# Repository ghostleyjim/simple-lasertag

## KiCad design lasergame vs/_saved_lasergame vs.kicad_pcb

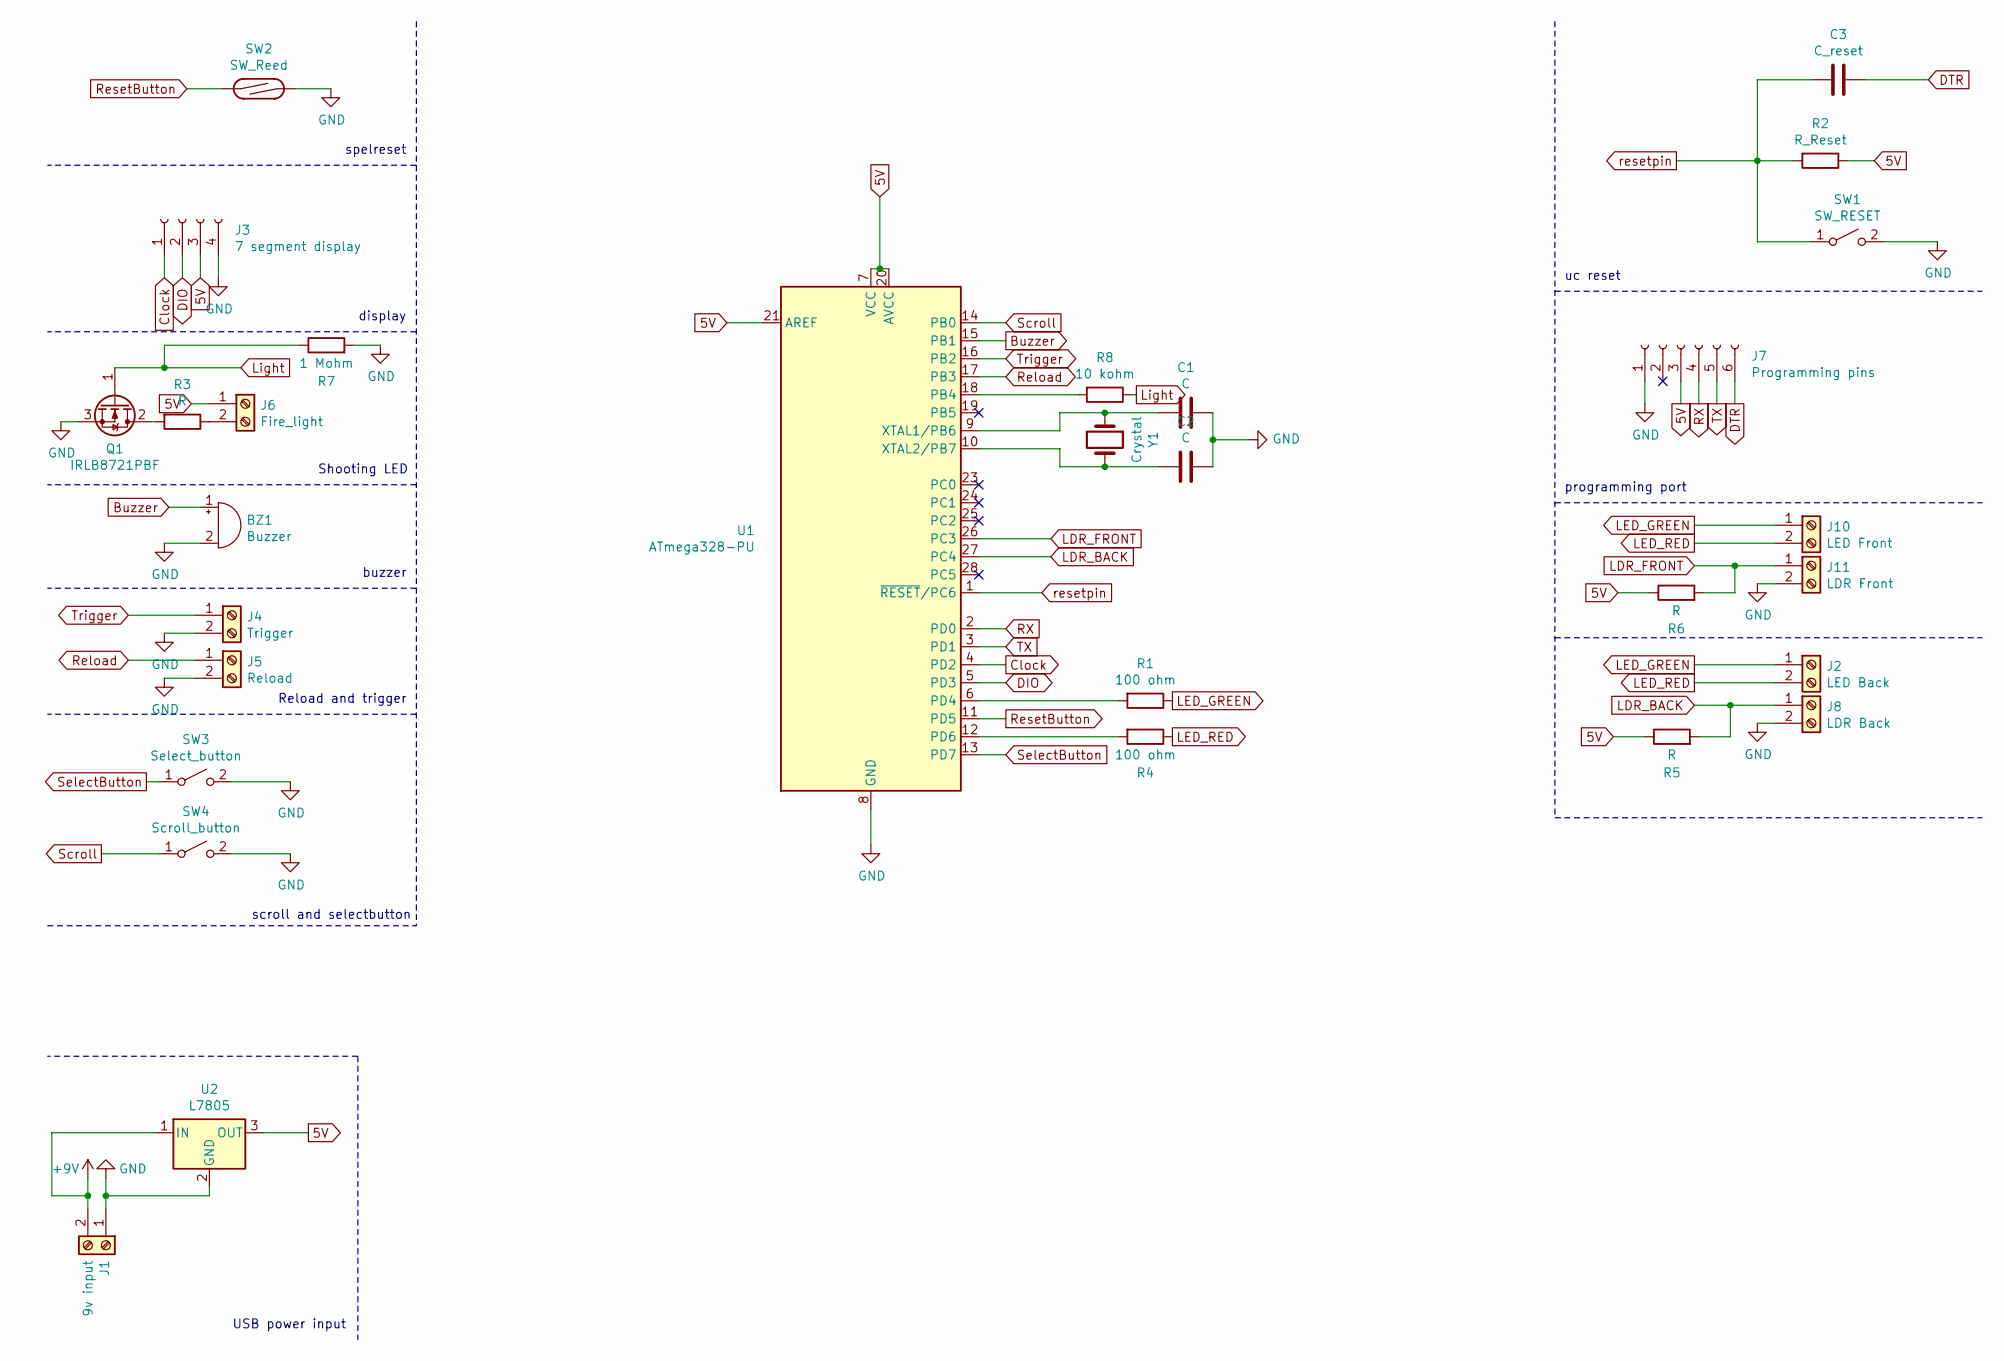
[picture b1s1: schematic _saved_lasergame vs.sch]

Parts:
BZ1: Buzzer; Buzzer_12x9.5RM7.6
C1, C2: C; C_Disc_D5.0mm_W2.5mm_P2.50mm
C3: C_reset; C_Disc_D5.0mm_W2.5mm_P2.50mm
J1: 9v input; TerminalBlock_Phoenix_MKDS-1,5-2-5.08_1x02_P5.08mm_Horizont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
J2: LED Back; TerminalBlock_Phoenix_MKDS-1,5-2-5.08_1x02_P5.08mm_Horizont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
J3: 7 segment display; PinHeader_1x04_P2.54mm_Vertical
J4: Trigger; TerminalBlock_Phoenix_MKDS-1,5-2-5.08_1x02_P5.08mm_Horizont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
J5: Reload; TerminalBlock_Phoenix_MKDS-1,5-2-5.08_1x02_P5.08mm_Horizont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
J6: Fire_light; TerminalBlock_Phoenix_MKDS-1,5-2-5.08_1x02_P5.08mm_Horizont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
J7: Programming pins; PinHeader_1x06_P2.54mm_Vertical
J8: LDR Back; TerminalBlock_Phoenix_MKDS-1,5-2-5.08_1x02_P5.08mm_Horizont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
J10: LED Front; TerminalBlock_Phoenix_MKDS-1,5-2-5.08_1x02_P5.08mm_Horizont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
J11: LDR Front; TerminalBlock_Phoenix_MKDS-1,5-2-5.08_1x02_P5.08mm_Horizont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
Q1: IRLB8721PBF; TO-220-3_Vertical
R1, R4: 100 ohm; R_Axial_DIN0309_L9.0mm_D3.2mm_P12.70mm_Horizontal
R2: R_Reset; R_Axial_DIN0309_L9.0mm_D3.2mm_P12.70mm_Horizontal
R3: R; R_Axial_DIN0516_L15.5mm_D5.0mm_P20.32mm_Horizontal
R5, R6: R; R_Axial_DIN0309_L9.0mm_D3.2mm_P12.70mm_Horizontal
R7: 1 Mohm; R_Axial_DIN0309_L9.0mm_D3.2mm_P12.70mm_Horizontal
R8: 10 kohm; R_Axial_DIN0309_L9.0mm_D3.2mm_P12.70mm_Horizontal
SW1: SW_RESET; SW_PUSH_6mm_H9.5mm
SW2: SW_Reed; Reed Switch THT
SW3: Select_button; SW_PUSH_6mm_H9.5mm
SW4: Scroll_button; SW_PUSH_6mm_H9.5mm
U1: ATmega328-PU; DIP-28_W7.62mm_Socket
U2: L7805; TO-220-3_Vertical
Y1: Crystal; Crystal_HC49-U_Vertical

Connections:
5V: J3.3, J6.1, J7.3, R2.1, R5.1, R6.1, U1.7 (VCC), U1.20 (AVCC), U1.21 (AREF), U2.3 (OUT)
+9V: J1.2, U2.1 (IN)
Buzzer: BZ1.1 (-), U1.15 (PB1)
Clock: J3.1, U1.4 (PD2)
DIO: J3.2, U1.5 (PD3)
DTR: C3.1, J7.6
GND: BZ1.2 (+), C1.1, C2.1, J1.1, J3.4, J4.2, J5.2, J7.1, J8.2, J11.2, Q1.3 (S), R7.2, SW1.2 (B), SW2.2, SW3.2 (B), SW4.2 (B), U1.8 (GND), U1.22 (GND), U2.2 (GND)
LDR_BACK: J8.1, R5.2, U1.27 (PC4)
LDR_FRONT: J11.1, R6.2, U1.26 (PC3)
LED_GREEN: J2.1, J10.1, R1.1
LED_RED: J2.2, J10.2, R4.1
Light: Q1.1 (G), R7.1, R8.1
unnamed: C1.2, U1.9 (XTAL1/PB6), Y1.1
unnamed: C2.2, U1.10 (XTAL2/PB7), Y1.2
unnamed: J6.2, R3.1
unnamed: Q1.2 (D), R3.2
unnamed: R1.2, U1.6 (PD4)
unnamed: R4.2, U1.12 (PD6)
unnamed: R8.2, U1.18 (PB4)
RX: J7.4, U1.2 (PD0)
Reload: J5.1, U1.17 (PB3)
ResetButton: SW2.1, U1.11 (PD5)
Scroll: SW4.1 (A), U1.14 (PB0)
SelectButton: SW3.1 (A), U1.13 (PD7)
TX: J7.5, U1.3 (PD1)
Trigger: J4.1, U1.16 (PB2)
resetpin: C3.2, R2.2, SW1.1 (A), U1.1 (~RESET~/PC6)

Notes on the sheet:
display
spelreset
uc reset
programming port
Shooting LED
USB power input
buzzer
Reload and trigger
scroll and selectbutton

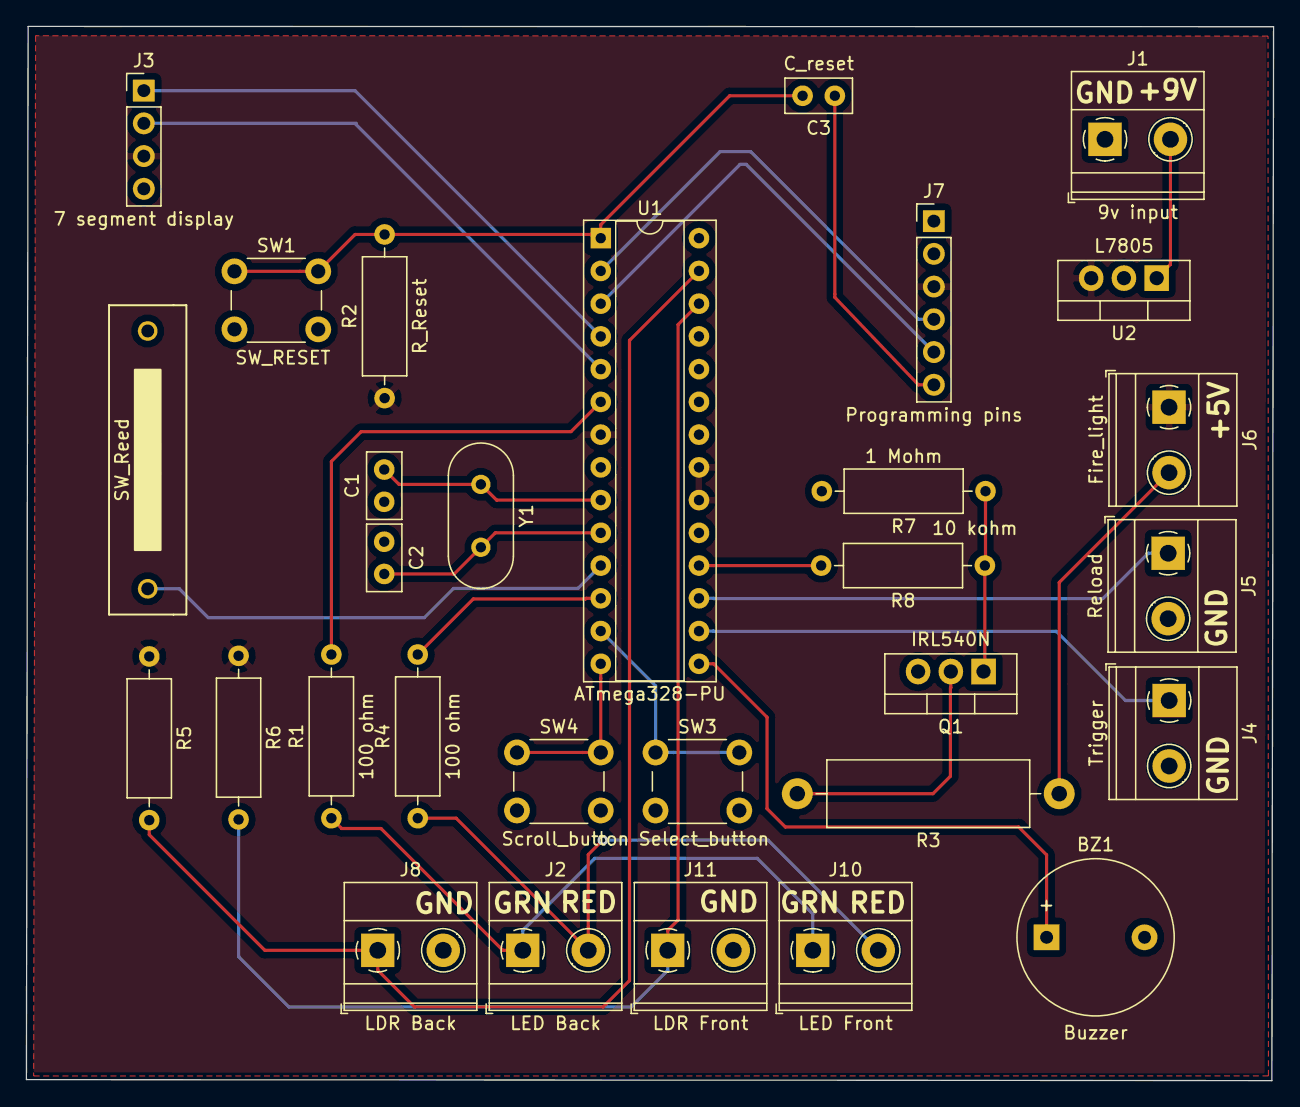
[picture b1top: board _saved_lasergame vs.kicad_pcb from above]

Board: 2 copper layers, 96.8 x 81.8 mm, 30 parts (0 on the bottom side), 27 nets.

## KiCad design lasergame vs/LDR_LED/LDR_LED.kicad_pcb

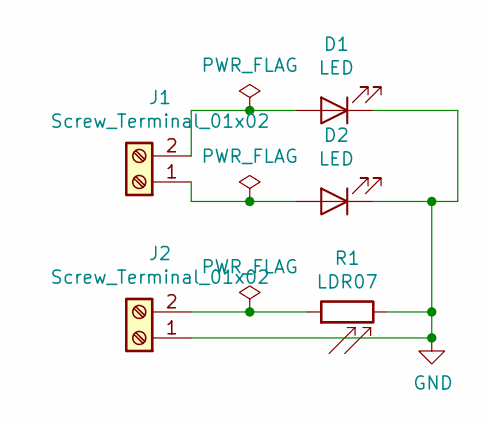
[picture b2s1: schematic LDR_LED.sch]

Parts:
D1, D2: LED; LED_D3.0mm
J1, J2: Screw_Terminal_01x02; TerminalBlock_Phoenix_MKDS1.5-2pol
R1: LDR07; R_LDR_5.1x4.3mm_P3.4mm_Vertical

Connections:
GND: D1.1 (K), D2.1 (K), J2.1, R1.2
unnamed: D1.2 (A), J1.2
unnamed: D2.2 (A), J1.1
unnamed: J2.2, R1.1

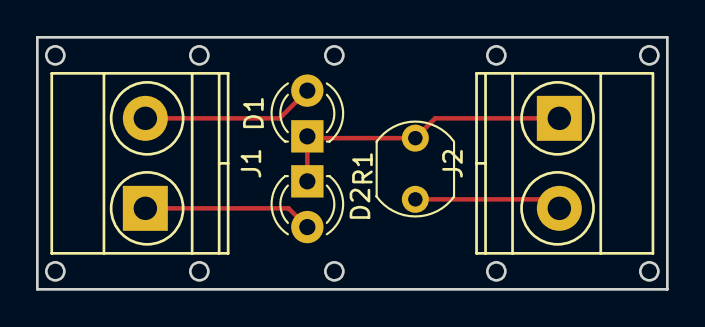
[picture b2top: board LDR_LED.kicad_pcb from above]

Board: 2 copper layers, 35.0 x 14.0 mm, 5 parts (0 on the bottom side), 4 nets.

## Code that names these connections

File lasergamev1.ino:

/* 
TO DO
- ontvangst lichtsensor en hitdetectie
- Team LED Not Working
- Ammo counter DONE
- powerups??
*/

#include "TM1637.h"

#include <Arduino.h>
#include <avr/power.h>

#define CLK 2
#define DIO 3

#define PIN 6
#define NUMPIXELS 3

// Input definition
#define SelectButton 7
#define ScrollButton 8
#define HitButton 4
#define ResetButton 5
#define TriggerPin 10
#define ReloadPin 11

//output definition
#define BuzzerPin 9
#define LightPin 12
#define RedLED 4
#define GreenLED 6

//analog input definition
#define LDR_Front A1
#define LDR_Back A2

// debounce and wait times
#define ButWaitTime 500     //wait time between buttonpresses
#define HitTime 1500        //cooldown time before you can get hit again and buzzersound time
unsigned long CooldownTime; // variable to store the millis() time
unsigned long LightTime;    // store millis() when LED is switched on

int LightOnTime = 1500; // time light is on (1000 ms is 1 sec)
int SemiMode = 500;     // time between being able to fire again.

int measurement_front[] = {0, 0, 0};
int measurement_back[] = {0, 0, 0};

int front = 0; //store average from measurement_front array to compare
int back = 0; //store average from measurement_back array to compare

bool PreviousTriggerState;

#define CLK 2//pins definitions for TM1637 and can be changed to other ports
#define DIO 3
TM1637 dis(CLK,DIO);

int8_t DisplayCode[] = {0x00, 0x00, 0x00, 0x00};

int Lives = 0; //global variable for startlives
int AmmoCount;
int Ammo = 20;         //ammount of ammo change variable for changing ammo per clip
bool StartFlag = true; // flag to run a setup in the beginning out of the void setup() function
bool DisplayState = true;
bool teamSelectFlag = false;

void setup()
{
  //initialize display
  dis.set(2); 
  dis.init();
  dis.point(POINT_ON);
    
  // pinmode definitions
  pinMode(SelectButton, INPUT_PULLUP);
  pinMode(ScrollButton, INPUT_PULLUP);
  
  pinMode(HitButton, INPUT_PULLUP);
  pinMode(ResetButton, INPUT_PULLUP);
  pinMode(ReloadPin, INPUT_PULLUP);
  
  pinMode(LDR_Front, INPUT);
  pinMode(LDR_Back, INPUT);
  
  pinMode(BuzzerPin, OUTPUT);
 
  pinMode(GreenLED, OUTPUT);
  pinMode(RedLED, OUTPUT);
  

  digitalWrite(GreenLED, HIGH);
  
  AmmoCount = Ammo;

for (int i = 0; i<=2; i++){ 																//take 3 readings from LDR and store in array
																										// check if for loop can be used in setup
	measurement_front[i] = analogRead(LDR_Front);
	
	Serial.print("measurement front no ");
	Serial.print(i);
	Serial.print(" = ");
	Serial.println(measurement_front[i]);

	delay(100);
	
	measurement_back[i] = analogRead(LDR_Back);
	
	Serial.print("measurement back no ");
	Serial.print(i);
	Serial.print(" = ");
	Serial.println(measurement_back[i]);
	
	delay(100);
}

front = (measurement_front[0] + measurement_front[1] + measurement_front[2]) / 3;

back = (measurement_back[0] + measurement_back[1] + measurement_back[2]) / 3;

Serial.print("measured average front = ");
Serial.println(front);

Serial.print("measured average back = ");
Serial.println(back);

Serial.begin(9600);
}

void loop()
{
  if (StartFlag == true)
  {
    GameStart();
  }
  
  

  if (Lives > 0 && StartFlag == false)
  {
    DisplayUpdate();
  dis.display(DisplayCode);
  
    Trigger();
    HitDetect();

    if (digitalRead(ReloadPin) == LOW)
    {
      AmmoCount = 20;
    }
  
  }
  else if (Lives == 0 && StartFlag == false)
  {
    for(int i=0; i<=3; i++)
    {
    DisplayCode[i] = 0x00 ;
    }
    GameEnd();
  }
}

// setup for game starting
void GameStart()
{
 while (teamSelectFlag == false) // first select teamcolor LED
  {
    if (digitalRead(ScrollButton) == LOW && millis() - CooldownTime >= ButWaitTime)
      {
        if (digitalRead(RedLED) == HIGH)
        {
          digitalWrite(RedLED, LOW);
          digitalWrite(GreenLED, HIGH);
          CooldownTime = millis();
        }
        else
        {
          digitalWrite(RedLED, HIGH);
          digitalWrite(GreenLED, LOW);
          CooldownTime = millis();
        }
        }
       
	    if (digitalRead(SelectButton) == LOW)
          {
        teamSelectFlag = true;
        Serial.println("Teamselectflag checked, let's continue ");
      }
  }
  


  while (StartFlag == true)
  {
     if (digitalRead(ScrollButton) == LOW && millis() - CooldownTime >= ButWaitTime)
    {
      Lives++;
      CooldownTime = millis();
      DisplayUpdate();
  dis.display(DisplayCode);
  Serial.println(Lives);
    }
      if (Lives >= 16)
      {
        Lives = 0;
        DisplayUpdate();
  dis.display(DisplayCode);
      }
    else if (digitalRead(SelectButton) == LOW && Lives > 0 && millis() - CooldownTime >= ButWaitTime)
    {
      StartFlag = false;
    }
  }
}


  void HitDetect()
  {

    if ((analogRead(LDR_Front) < Front || analogRead(LDR_Back) < Back) && millis() - CooldownTime >= HitTime ) //check if LDR measurement gets higher or lower
    {
	  Lives--;
      CooldownTime = millis();
      tone(BuzzerPin, 800, HitTime);
    }
  }



  void GameEnd()
  {
    if (digitalRead(ResetButton) == LOW)
    {
      StartFlag = true;
      loop();
    }

    if (millis() - CooldownTime >= 1000)
    {

      if (DisplayState == true)
      {
        DisplayState = false;
      }
      else
      {
        DisplayState = true;
      }
      CooldownTime = millis();
    }
    if (DisplayState == true)
    {
      dis.init();
      tone(BuzzerPin, 400, 500);
    }
    else
    {
      dis.display(DisplayCode);
      tone(BuzzerPin, 800, 500);
    }
  }

  void Trigger()
  {

    bool TriggerPinState;

    TriggerPinState = digitalRead(TriggerPin);

        if (TriggerPinState == LOW && PreviousTriggerState != TriggerPinState && AmmoCount > 0 && millis() - LightTime >= (LightOnTime + SemiMode))
    {
      digitalWrite(LightPin, HIGH);
      Serial.println("fire!");
      AmmoCount--;
      LightTime = millis();
    }
	
    if (millis() - LightTime >= LightOnTime)
    {
      digitalWrite(LightPin, LOW);
    }

    PreviousTriggerState = TriggerPinState;
  }

  void Reload()
  {
    if (digitalRead(ReloadPin) == LOW && AmmoCount <= 3 && CooldownTime >= ButWaitTime)
    {
      AmmoCount = Ammo;
      CooldownTime = millis();
    }
  }

  void DisplayUpdate()
  {
DisplayCode[0] = AmmoCount / 10;
DisplayCode[1] = AmmoCount % 10;
DisplayCode[2] = Lives / 10;
DisplayCode[3] = Lives % 10 ;
  } 

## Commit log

2019-01-19 wijziging 19 jan 2019
2019-01-20 PCB files started
2019-01-21 updated the schematics
2019-01-25 updated schematics, 2nd PCB for LDR's and LED's
2019-01-25 added LDR measuring and hitdetection need to check if LDR reading goes higher or lower when hit by light.
2019-01-25 also check red and green LED resistor and add them
2019-01-25 cleaned a bit up and changed some position of the code around
2019-02-15 removed some test code because it works as intended. cleaned up some code and resolved issue with mosfet not working (did not define pullup on triggerpin)
2019-02-17 first prototype pcb ordered
2019-03-05 cleaned up code a bit
2019-04-28 removed display flickering
2019-04-29 fixed the display not turning on after game reset and put user changeable variables on top.
